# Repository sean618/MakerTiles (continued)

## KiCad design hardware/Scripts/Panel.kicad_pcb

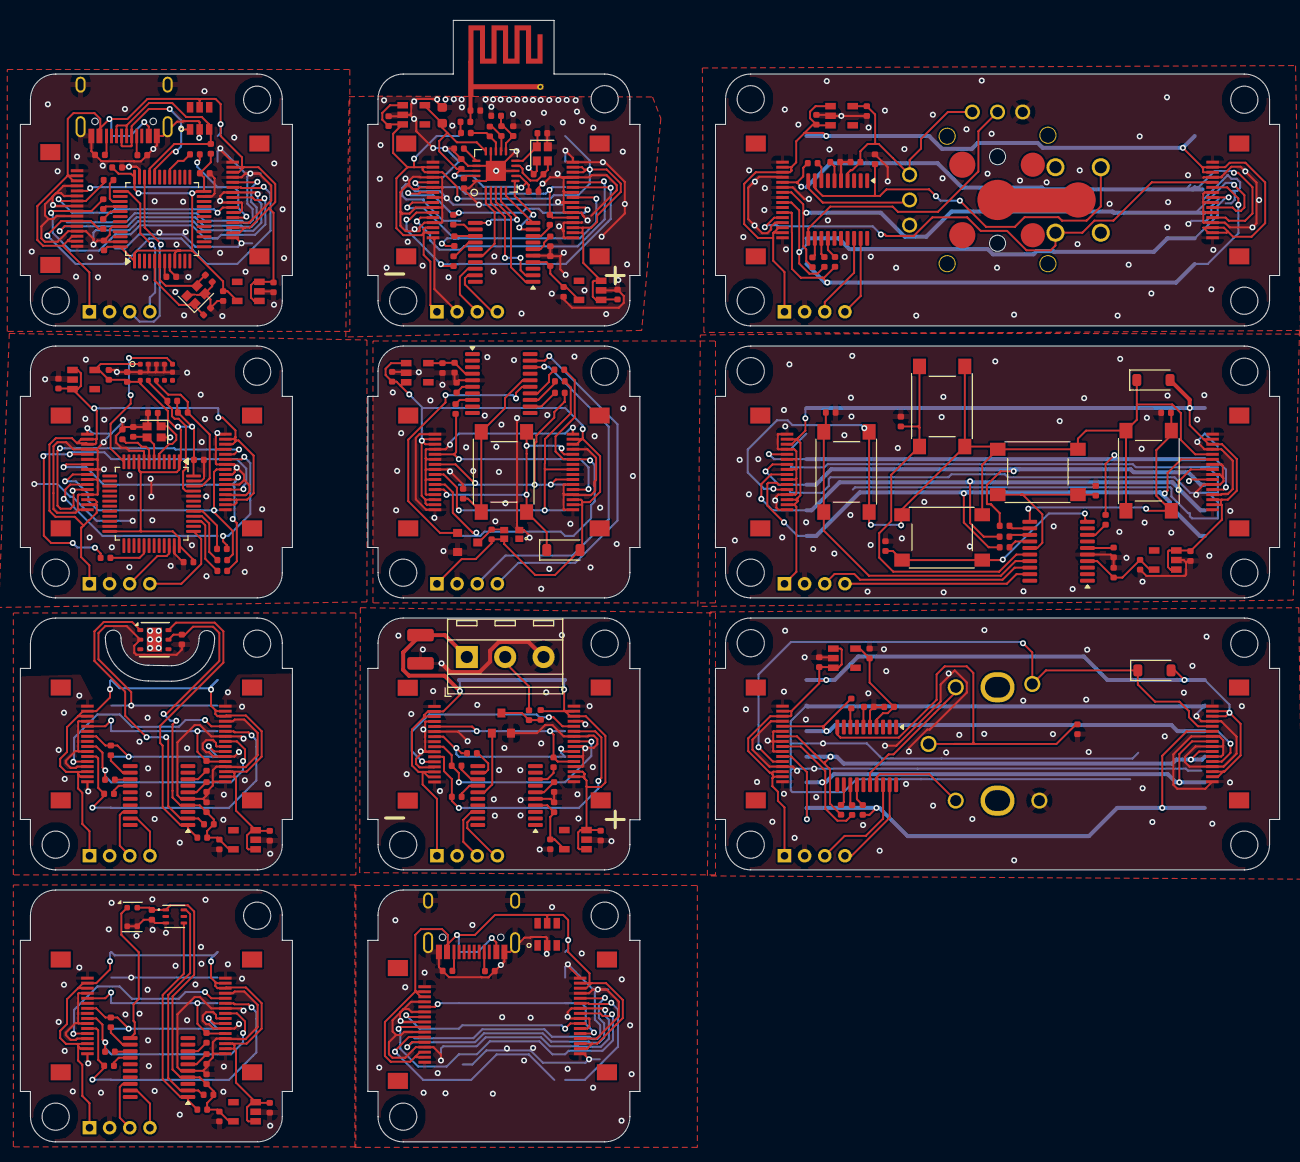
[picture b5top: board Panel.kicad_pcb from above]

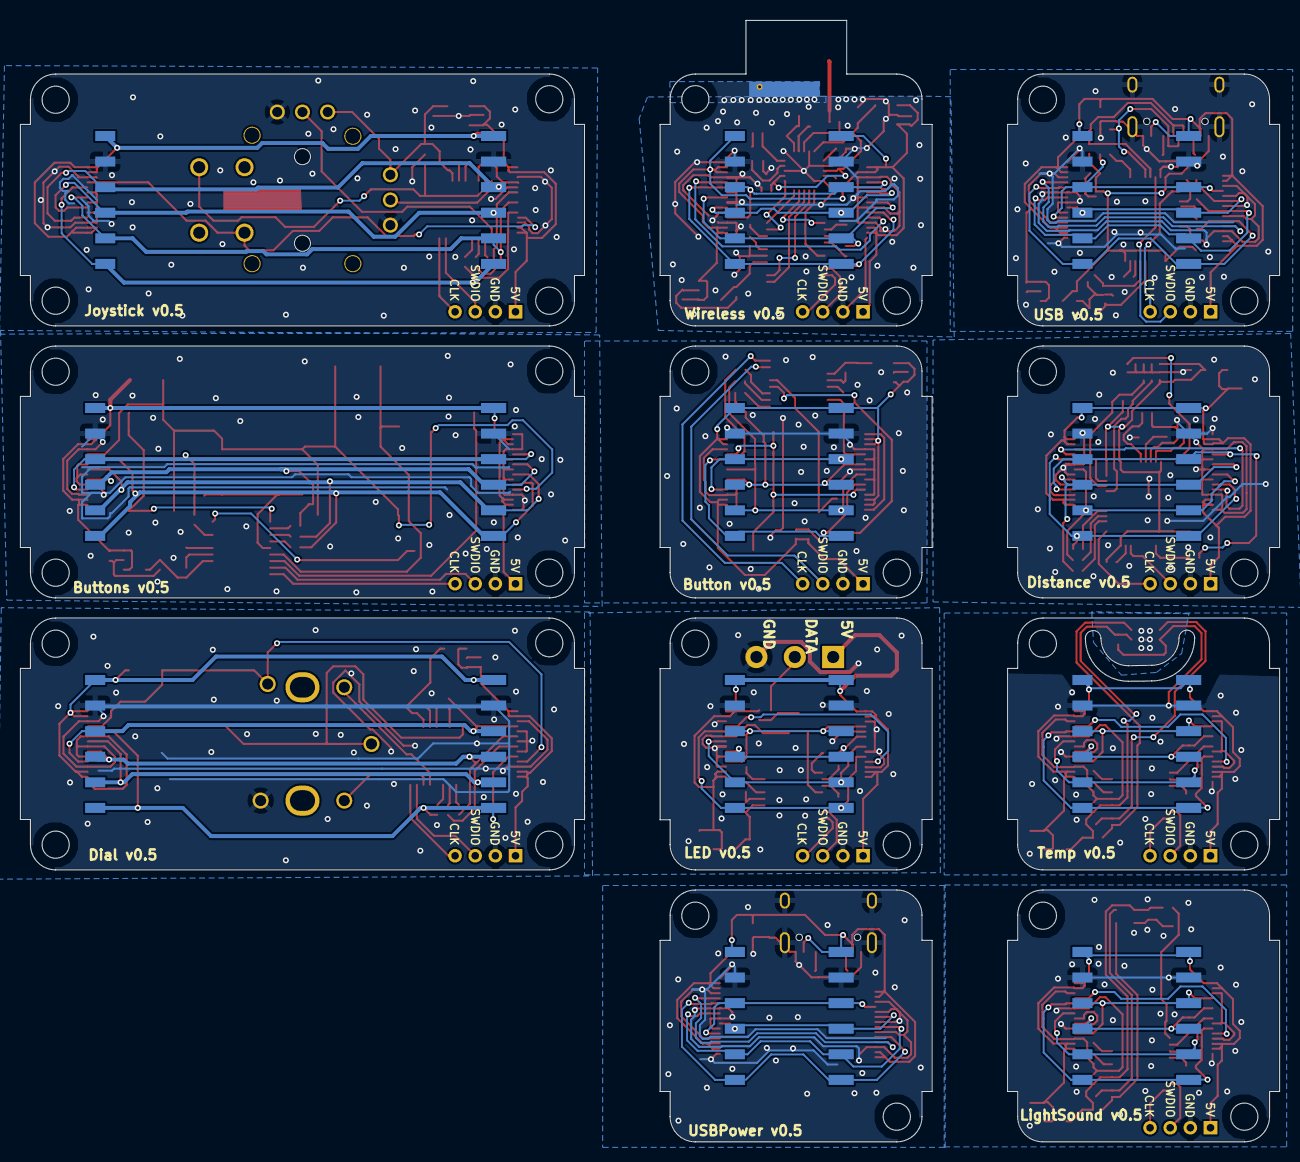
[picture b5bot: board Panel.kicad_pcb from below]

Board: 4 copper layers, 125.0 x 111.3 mm, 273 parts (22 on the bottom side), 208 nets.

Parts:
BTSC1: 0.1uF; C_0402_1005Metric
BTSC2, BTSC8, BTSC9: 4.7uF; C_0402_1005Metric
BTSD2: 1N4148W; D_SOD-123
BTSH1, BTSH2, BTSH3, BTSH4: M2.5MountingHole; MountingHole_2.7mm_M2.5_ISO7380
BTSIGNORE1: Buttons v0.5; BoardText
BTSJ1: 01x06_2.54mm_Male
BTSJ2: 01x06_2.54mm_Female
BTSJ3, BTSJ5: FFC_connector_16p_hinge_lock
BTSJ4: swd_4pin; swd_header
BTSR1, BTSR2, BTSR3, BTSR4: 75R; R_0402_1005Metric
BTSR5, BTSR6, BTSR7, BTSR8, BTSR9: 10K; R_0402_1005Metric
BTSSW1, BTSSW2, BTSSW3, BTSSW4, BTSSW6: button_6x6x7; SW_SPST_PTS645
BTSU2: ME6211C33M5G-N; SOT-23-5
BTSU3: STM32G030F6P6; TSSOP-20_4.4x6.5mm_P0.65mm
BUTC1: 0.1uF; C_0402_1005Metric
BUTC2, BUTC8, BUTC9: 4.7uF; C_0402_1005Metric
BUTD2: ws2812b_1615; WS2812B_1615
BUTD3: 1N4148W; D_SOD-123
BUTH1, BUTH2: M2.5MountingHole; MountingHole_2.7mm_M2.5_ISO7380
BUTIGNORE1: Button v0.5; BoardText
BUTJ1, BUTJ3: FFC_connector_16p_hinge_lock
BUTJ2: 01x06_2.54mm_Male
BUTJ4: swd_4pin; swd_header
BUTJ5: 01x06_2.54mm_Female
BUTQ1: N_MOSFET; SOT-23
BUTR1, BUTR2, BUTR3, BUTR4: 75R; R_0402_1005Metric
BUTR5: 10K; R_0402_1005Metric
BUTR6: 1K; R_0402_1005Metric
BUTSW2: button_6x6x7; SW_SPST_PTS645
BUTU2: ME6211C33M5G-N; SOT-23-5
BUTU3: STM32G030F6P6; TSSOP-20_4.4x6.5mm_P0.65mm
DIAC1: 0.1uF; C_0402_1005Metric
DIAC2, DIAC8, DIAC9: 4.7uF; C_0402_1005Metric
DIAD2: 1N4148W; D_SOD-123
DIAH1, DIAH2, DIAH3, DIAH4: M2.5MountingHole; MountingHole_2.7mm_M2.5_ISO7380
DIAIGNORE1: Dial v0.5; BoardText
DIAJ1, DIAJ2: FFC_connector_16p_hinge_lock
DIAJ3: 01x06_2.54mm_Male
DIAJ4: swd_4pin; swd_header
DIAJ5: 01x06_2.54mm_Female
DIAR1, DIAR2, DIAR3, DIAR4: 75R; R_0402_1005Metric
DIAR5: 10K; R_0402_1005Metric
DIASW7: RotaryEncoder_Switch; RotaryEncoderEC12D
DIAU2: ME6211C33M5G-N; SOT-23-5
DIAU3: STM32G030F6P6; TSSOP-20_4.4x6.5mm_P0.65mm
DISC3, DISC4, DISC5, DISC8, DISC9: 4.7uF; C_0402_1005Metric
DISC6, DISC7: 12pF; C_0402_1005Metric
DISC11: 0.1uF; C_0402_1005Metric
DISH1, DISH2: M2.5MountingHole; MountingHole_2.7mm_M2.5_ISO7380
DISIGNORE1: Distance v0.5; BoardText
DISJ1: 01x06_2.54mm_Male
DISJ2: 01x06_2.54mm_Female
DISJ3, DISJ5: FFC_connector_16p_hinge_lock
DISJ4: swd_4pin; swd_header
DISR5, DISR6: 10K; R_0402_1005Metric
DISR7, DISR8, DISR9, DISR10: 75R; R_0402_1005Metric
DISU1: VL53L3CXV0DH
DISU2: ME6211C33M5G-N; SOT-23-5
DISU3: STM32F103C8T6; LQFP-48_7x7mm_P0.5mm
DISY1: Crystal_16M_small; Crystal_SMD_2016-4Pin_2.0x1.6mm
JOYC1: 0.1uF; C_0402_1005Metric
JOYC2, JOYC8, JOYC9: 4.7uF; C_0402_1005Metric
JOYH1, JOYH2, JOYH3, JOYH4: M2.5MountingHole; MountingHole_2.7mm_M2.5_ISO7380
JOYIGNORE1: Joystick v0.5; BoardText
JOYJ1: 01x06_2.54mm_Male
JOYJ2, JOYJ5: FFC_connector_16p_hinge_lock
JOYJ3: 01x06_2.54mm_Female
JOYJ4: swd_4pin; swd_header
JOYR1, JOYR2, JOYR3, JOYR4: 75R; R_0402_1005Metric
JOYR6: 10K; R_0402_1005Metric
JOYU1: Joystick
JOYU2: ME6211C33M5G-N; SOT-23-5
JOYU3: STM32G030F6P6; TSSOP-20_4.4x6.5mm_P0.65mm
LEDC1: 0.1uF; C_0402_1005Metric
LEDC2, LEDC8, LEDC9: 4.7uF; C_0402_1005Metric
LEDC4: 47uF_16V; C_1210_3225Metric
LEDH1, LEDH2: M2.5MountingHole; MountingHole_2.7mm_M2.5_ISO7380
LEDIGNORE1: LED v0.5; BoardText
LEDIGNORE2: GND; BoardText
LEDIGNORE3: DATA; BoardText
LEDIGNORE4: 5V; BoardText
LEDJ1: 01x06_2.54mm_Male
LEDJ2: TerminalBlock_3P_3.8_black; TerminalBlock_03_P3.81mm_Horizontal
LEDJ3: 01x06_2.54mm_Female
LEDJ4: swd_4pin; swd_header
LEDJ5, LEDJ7: FFC_connector_16p_hinge_lock
LEDQ3: N_MOSFET; SOT-23
LEDR1, LEDR2, LEDR3, LEDR4: 75R; R_0402_1005Metric
LEDR5, LEDR7: 1K; R_0402_1005Metric
LEDU2: ME6211C33M5G-N; SOT-23-5
LEDU3: STM32G030F6P6; TSSOP-20_4.4x6.5mm_P0.65mm
LIGC1: 0.1uF; C_0402_1005Metric
LIGC2, LIGC3, LIGC8, LIGC9: 4.7uF; C_0402_1005Metric
LIGH1, LIGH2: M2.5MountingHole; MountingHole_2.7mm_M2.5_ISO7380
LIGIGNORE1: LightSound v0.5; BoardText
LIGJ1: 01x06_2.54mm_Male
LIGJ2: 01x06_2.54mm_Female
LIGJ3, LIGJ5: FFC_connector_16p_hinge_lock
LIGJ4: swd_4pin; swd_header
LIGR1, LIGR2, LIGR3, LIGR4: 75R; R_0402_1005Metric
LIGR5, LIGR6: 10K; R_0402_1005Metric
LIGU1: LTR-381RGB
LIGU2: ME6211C33M5G-N; SOT-23-5
LIGU3: STM32G030F6P6; TSSOP-20_4.4x6.5mm_P0.65mm
LIGU4: WMM7027ATSN1-4/TR; LGA-4
POWH1, POWH2: M2.5MountingHole; MountingHole_2.7mm_M2.5_ISO7380
POWIC1: USBLC6-4SC6; SOT-23-6
POWIGNORE1: USBPower v0.5; BoardText
POWJ1: 01x06_2.54mm_Male
POWJ2: USB_C_connector_16P; USB_C_Receptacle_16P
POWJ3: 01x06_2.54mm_Female
POWJ5, POWJ6: FFC_connector_16p_hinge_lock
POWR1, POWR2: 5.1K; R_0402_1005Metric
TMPC1: 0.1uF; C_0402_1005Metric
TMPC2, TMPC3, TMPC8, TMPC9: 4.7uF; C_0402_1005Metric
TMPH1, TMPH2: M2.5MountingHole; MountingHole_2.7mm_M2.5_ISO7380
TMPIGNORE1: Temp v0.5; BoardText
TMPJ1: 01x06_2.54mm_Male
TMPJ2: 01x06_2.54mm_Female
TMPJ3, TMPJ5: FFC_connector_16p_hinge_lock
TMPJ4: swd_4pin; swd_header
TMPR1, TMPR2, TMPR3, TMPR4: 75R; R_0402_1005Metric
TMPR5, TMPR6: 10K; R_0402_1005Metric
TMPU1: HDC1080; Texas_PWSON-N6
TMPU2: ME6211C33M5G-N; SOT-23-5
TMPU3: STM32G030F6P6; TSSOP-20_4.4x6.5mm_P0.65mm
USBC1, USBC2, USBC5, USBC8, USBC9: 4.7uF; C_0402_1005Metric
USBC4: 0.1uF; C_0402_1005Metric
USBC6, USBC7: 12pF; C_0402_1005Metric
USBH1, USBH2: M2.5MountingHole; MountingHole_2.7mm_M2.5_ISO7380
USBIC1: USBLC6-4SC6; SOT-23-6
USBIGNORE1: USB v0.5; BoardText
USBJ1: 01x06_2.54mm_Male
USBJ2: USB_C_connector_16P; USB_C_Receptacle_16P
USBJ3: 01x06_2.54mm_Female
USBJ4: swd_4pin; swd_header
USBJ5, USBJ6: FFC_connector_16p_hinge_lock
USBR1, USBR2: 5.1K; R_0402_1005Metric
USBR4, USBR5, USBR6, USBR7: 75R; R_0402_1005Metric
USBR12: 1.5K; R_0402_1005Metric
USBU1: STM32F103C8T6; LQFP-48_7x7mm_P0.5mm
USBU2: ME6211C33M5G-N; SOT-23-5
USBY2: Crystal_16M_small; Crystal_SMD_2016-4Pin_2.0x1.6mm
WIRAE1: Antenna_MIFA_Cypress; Antenna_cypress_MIFA
WIRC1: 0.1uF; C_0402_1005Metric
WIRC2, WIRC8, WIRC9, WIRC11, WIRC12, WIRC15: 4.7uF; C_0402_1005Metric
WIRC3: 33nF; C_0402_1005Metric
WIRC4: 2.2nF; C_0402_1005Metric
WIRC5, WIRC6: 12pF; C_0402_1005Metric
WIRC7: 1pF; C_0402_1005Metric
WIRC10: 1.5pF; C_0402_1005Metric
WIRC13: 22uF_10V; C_0603_1608Metric
WIRC14: 4.7pF; C_0402_1005Metric
WIRH1, WIRH2: M2.5MountingHole; MountingHole_2.7mm_M2.5_ISO7380
WIRIGNORE1: Wireless v0.5; BoardText
WIRJ1: 01x06_2.54mm_Male
WIRJ2: 01x06_2.54mm_Female
WIRJ3, WIRJ5: FFC_connector_16p_hinge_lock
WIRJ4: swd_4pin; swd_header
WIRL1: 8.2nH; C_0402_1005Metric
WIRL3: 3.9nH; C_0402_1005Metric
WIRL4: 2.7nH; C_0402_1005Metric
WIRR1, WIRR2, WIRR3, WIRR4: 120R; R_0402_1005Metric
WIRR6: 22K; R_0402_1005Metric
WIRU1, WIRU2: ME6211C33M5G-N; SOT-23-5
WIRU3: STM32G030F6P6; TSSOP-20_4.4x6.5mm_P0.65mm
WIRU4: NRF24L01; QFN-20-1EP_4x4mm_P0.5mm_EP2.5x2.5mm
WIRY2: Crystal_16M_small; Crystal_SMD_2016-4Pin_2.0x1.6mm

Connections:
BTS_5V: BTSC8.1, BTSD2.2 (A), BTSJ1.1, BTSJ2.6, BTSJ3.2, BTSJ3.3, BTSJ3.14, BTSJ3.15, BTSJ4.1, BTSJ5.2, BTSJ5.3, BTSJ5.14, BTSJ5.15, BTSU2.1 (IN), BTSU2.3 (EN)
BTS_GND: BTSC1.2, BTSC2.2, BTSC8.2, BTSC9.2, BTSJ1.2, BTSJ2.5, BTSJ3.1, BTSJ3.4, BTSJ3.6, BTSJ3.8, BTSJ3.10, BTSJ3.13, BTSJ3.16, BTSJ4.2, BTSJ5.1, BTSJ5.4, BTSJ5.6, BTSJ5.8, BTSJ5.10, BTSJ5.13, BTSJ5.16, BTSR5.1, BTSR6.1, BTSR7.1, BTSR8.1, BTSR9.1, BTSU2.2 (GND), BTSU3.5 (VSS)
BTS_Interrupt5V: BTSD2.1 (K), BTSJ3.12, BTSJ5.12, BTSSW1.2, BTSSW2.2, BTSSW3.2, BTSSW4.2, BTSSW6.2
BTS_MISO: BTSJ1.5, BTSJ2.2, BTSJ3.9, BTSJ5.9, BTSR4.2
BTS_MOSI: BTSJ1.6, BTSJ2.1, BTSJ3.11, BTSJ5.11, BTSR2.2
BTS_Net-(U3-NRST): BTSC1.1, BTSU3.6 (NRST)
BTS_Net-(U3-PA1): BTSR1.1, BTSU3.8 (PA1)
BTS_Net-(U3-PA5): BTSR3.1, BTSU3.12 (PA5)
BTS_Net-(U3-PA6): BTSR4.1, BTSU3.13 (PA6)
BTS_Net-(U3-PA7): BTSR2.1, BTSU3.14 (PA7)
BTS_PS: BTSJ1.3, BTSJ2.4, BTSJ3.5, BTSJ5.5, BTSR1.2
BTS_SCLK: BTSJ1.4, BTSJ2.3, BTSJ3.7, BTSJ5.7, BTSR3.2
BTS_SW1: BTSR5.2, BTSSW2.1, BTSU3.16 (PA11/PA9)
BTS_SW2: BTSR6.2, BTSSW1.1, BTSU3.17 (PA12/PA10)
BTS_SW3: BTSR7.2, BTSSW6.1, BTSU3.11 (PA4)
BTS_SW4: BTSR9.2, BTSSW3.1, BTSU3.15 (PB0/PB1/PB2/PA8)
BTS_SW5: BTSR8.2, BTSSW4.1, BTSU3.10 (PA3)
BTS_SWDCLK: BTSJ4.4, BTSU3.19 (PA14/PA15)
BTS_SWDIO: BTSJ4.3, BTSU3.18 (PA13)
BTS_VDD: BTSC2.1, BTSC9.1, BTSU2.5 (OUT), BTSU3.4 (VDD)
BUT_5V: BUTC8.1, BUTD2.2 (VDD), BUTD3.2 (A), BUTJ1.2, BUTJ1.3, BUTJ1.14, BUTJ1.15, BUTJ2.1, BUTJ3.2, BUTJ3.3, BUTJ3.14, BUTJ3.15, BUTJ4.1, BUTJ5.6, BUTR6.1, BUTU2.1 (IN), BUTU2.3 (EN)
BUT_GND: BUTC1.2, BUTC2.2, BUTC8.2, BUTC9.2, BUTD2.3 (VSS), BUTJ1.1, BUTJ1.4, BUTJ1.6, BUTJ1.8, BUTJ1.10, BUTJ1.13, BUTJ1.16, BUTJ2.2, BUTJ3.1, BUTJ3.4, BUTJ3.6, BUTJ3.8, BUTJ3.10, BUTJ3.13, BUTJ3.16, BUTJ4.2, BUTJ5.5, BUTQ1.2 (S), BUTR5.1, BUTU2.2 (GND), BUTU3.5 (VSS)
BUT_Interrupt5V: BUTD3.1 (K), BUTJ1.12, BUTJ3.12, BUTSW2.2
BUT_LED_DATA: BUTQ1.1 (G), BUTU3.15 (PB0/PB1/PB2/PA8)
BUT_MISO: BUTJ1.9, BUTJ2.5, BUTJ3.9, BUTJ5.2, BUTR4.2
BUT_MOSI: BUTJ1.11, BUTJ2.6, BUTJ3.11, BUTJ5.1, BUTR2.2
BUT_Net-(D2-DIN): BUTD2.4 (DIN), BUTQ1.3 (D), BUTR6.2
BUT_Net-(U3-NRST): BUTC1.1, BUTU3.6 (NRST)
BUT_Net-(U3-PA1): BUTR1.1, BUTU3.8 (PA1)
BUT_Net-(U3-PA5): BUTR3.1, BUTU3.12 (PA5)
BUT_Net-(U3-PA6): BUTR4.1, BUTU3.13 (PA6)
BUT_Net-(U3-PA7): BUTR2.1, BUTU3.14 (PA7)
BUT_PS: BUTJ1.5, BUTJ2.3, BUTJ3.5, BUTJ5.4, BUTR1.2
BUT_SCLK: BUTJ1.7, BUTJ2.4, BUTJ3.7, BUTJ5.3, BUTR3.2
BUT_SW1: BUTR5.2, BUTSW2.1, BUTU3.16 (PA11/PA9)
BUT_SWDCLK: BUTJ4.4, BUTU3.19 (PA14/PA15)
BUT_SWDIO: BUTJ4.3, BUTU3.18 (PA13)
BUT_VDD: BUTC2.1, BUTC9.1, BUTU2.5 (OUT), BUTU3.4 (VDD)
DIA_5V: DIAC8.1, DIAD2.2 (A), DIAJ1.2, DIAJ1.3, DIAJ1.14, DIAJ1.15, DIAJ2.2, DIAJ2.3, DIAJ2.14, DIAJ2.15, DIAJ3.1, DIAJ4.1, DIAJ5.6, DIAU2.1 (IN), DIAU2.3 (EN)
DIA_ENC_A: DIASW7.A, DIAU3.17 (PA12/PA10)
DIA_ENC_B: DIASW7.B, DIAU3.16 (PA11/PA9)
DIA_GND: DIAC1.2, DIAC2.2, DIAC8.2, DIAC9.2, DIAJ1.1, DIAJ1.4, DIAJ1.6, DIAJ1.8, DIAJ1.10, DIAJ1.13, DIAJ1.16, DIAJ2.1, DIAJ2.4, DIAJ2.6, DIAJ2.8, DIAJ2.10, DIAJ2.13, DIAJ2.16, DIAJ3.2, DIAJ4.2, DIAJ5.5, DIAR5.1, DIASW7.C, DIAU2.2 (GND), DIAU3.5 (VSS)
DIA_Interrupt5V: DIAD2.1 (K), DIAJ1.12, DIAJ2.12, DIASW7.S1
DIA_MISO: DIAJ1.9, DIAJ2.9, DIAJ3.5, DIAJ5.2, DIAR4.2
DIA_MOSI: DIAJ1.11, DIAJ2.11, DIAJ3.6, DIAJ5.1, DIAR2.2
DIA_Net-(U3-NRST): DIAC1.1, DIAU3.6 (NRST)
DIA_Net-(U3-PA1): DIAR1.1, DIAU3.8 (PA1)
DIA_Net-(U3-PA5): DIAR3.1, DIAU3.12 (PA5)
DIA_Net-(U3-PA6): DIAR4.1, DIAU3.13 (PA6)
DIA_Net-(U3-PA7): DIAR2.1, DIAU3.14 (PA7)
DIA_PS: DIAJ1.5, DIAJ2.5, DIAJ3.3, DIAJ5.4, DIAR1.2
DIA_SCLK: DIAJ1.7, DIAJ2.7, DIAJ3.4, DIAJ5.3, DIAR3.2
DIA_SW1: DIAR5.2, DIASW7.S2, DIAU3.10 (PA3)
DIA_SWDCLK: DIAJ4.4, DIAU3.19 (PA14/PA15)
DIA_SWDIO: DIAJ4.3, DIAU3.18 (PA13)
DIA_VDD: DIAC2.1, DIAC9.1, DIAU2.5 (OUT), DIAU3.4 (VDD)
DIS_5V: DISC8.1, DISJ1.1, DISJ2.6, DISJ3.2, DISJ3.3, DISJ3.14, DISJ3.15, DISJ4.1, DISJ5.2, DISJ5.3, DISJ5.14, DISJ5.15, DISU2.1 (IN), DISU2.3 (EN)
DIS_GND: DISC3.2, DISC4.2, DISC5.2, DISC6.1, DISC7.1, DISC8.2, DISC9.2, DISC11.1, DISJ1.2, DISJ2.5, DISJ3.1, DISJ3.4, DISJ3.6, DISJ3.8, DISJ3.10, DISJ3.13, DISJ3.16, DISJ4.2, DISJ5.1, DISJ5.4, DISJ5.6, DISJ5.8, DISJ5.10, DISJ5.13, DISJ5.16, DISU1.2 (AVSSVCSEL), DISU1.3 (GND), DISU1.4 (GND), DISU1.6 (GND), DISU1.12 (GND), DISU2.2 (GND), DISU3.8 (VSSA), DISU3.23 (VSS), DISU3.35 (VSS), DISU3.44 (BOOT0), DISU3.47 (VSS), DISY1.2 (GND), DISY1.4 (GND)
DIS_Interrupt5V: DISJ3.12, DISJ5.12
DIS_MISO: DISJ1.5, DISJ2.2, DISJ3.9, DISJ5.9, DISR8.2
DIS_MISO_UC: DISR8.1, DISU3.40 (PB4)
DIS_MOSI: DISJ1.6, DISJ2.1, DISJ3.11, DISJ5.11, DISR9.2
DIS_MOSI_UC: DISR9.1, DISU3.41 (PB5)
DIS_Net-(U3-NRST): DISC11.2, DISU3.7 (NRST)
DIS_OSC_IN: DISC6.2, DISU3.5 (PD0), DISY1.1
DIS_OSC_OUT: DISC7.2, DISU3.6 (PD1), DISY1.3
DIS_PS: DISJ1.3, DISJ2.4, DISJ3.5, DISJ5.5, DISR10.2
DIS_PS_UC: DISR10.1, DISU3.29 (PA8)
DIS_SCL: DISR6.1, DISU1.10 (SCL), DISU3.45 (PB8)
DIS_SCLK: DISJ1.4, DISJ2.3, DISJ3.7, DISJ5.7, DISR7.2
DIS_SCLK_UC: DISR7.1, DISU3.39 (PB3)
DIS_SDA: DISR5.1, DISU1.9 (SDA), DISU3.46 (PB9)
DIS_SWDCLK: DISJ4.4, DISU3.37 (PA14)
DIS_SWDIO: DISJ4.3, DISU3.34 (PA13)
DIS_VDD: DISC3.1, DISC4.1, DISC5.1, DISC9.1, DISR5.2, DISR6.2, DISU1.1 (AVDDVCSEL), DISU1.11 (AVDD), DISU2.5 (OUT), DISU3.1 (VBAT), DISU3.9 (VDDA), DISU3.24 (VDD), DISU3.36 (VDD), DISU3.48 (VDD)
DIS_XSHUT: DISU1.5 (XSHUT), DISU3.12 (PA2)
JOY_5V: JOYC8.1, JOYJ1.1, JOYJ2.2, JOYJ2.3, JOYJ2.14, JOYJ2.15, JOYJ3.6, JOYJ4.1, JOYJ5.2, JOYJ5.3, JOYJ5.14, JOYJ5.15, JOYU2.1 (IN), JOYU2.3 (EN)
JOY_BUTTON: JOYR6.2, JOYU1.D (BUTTON4), JOYU3.9 (PA2)
JOY_GND: JOYC1.2, JOYC2.2, JOYC8.2, JOYC9.2, JOYJ1.2, JOYJ2.1, JOYJ2.4, JOYJ2.6, JOYJ2.8, JOYJ2.10, JOYJ2.13, JOYJ2.16, JOYJ3.5, JOYJ4.2, JOYJ5.1, JOYJ5.4, JOYJ5.6, JOYJ5.8, JOYJ5.10, JOYJ5.13, JOYJ5.16, JOYR6.1, JOYU1.3 (POT1_VLOW), JOYU1.6 (POT2_VLOW), JOYU2.2 (GND), JOYU3.5 (VSS)
JOY_HORIZONTAL: JOYU1.2 (POT1_OUT), JOYU3.11 (PA4)
JOY_Interrupt5V: JOYJ2.12, JOYJ5.12, JOYU1.A (BUTTON1)
JOY_MISO: JOYJ1.5, JOYJ2.9, JOYJ3.2, JOYJ5.9, JOYR4.2
JOY_MOSI: JOYJ1.6, JOYJ2.11, JOYJ3.1, JOYJ5.11, JOYR2.2
JOY_Net-(U3-NRST): JOYC1.1, JOYU3.6 (NRST)
JOY_Net-(U3-PA1): JOYR1.1, JOYU3.8 (PA1)
JOY_Net-(U3-PA5): JOYR3.1, JOYU3.12 (PA5)
JOY_Net-(U3-PA6): JOYR4.1, JOYU3.13 (PA6)
JOY_Net-(U3-PA7): JOYR2.1, JOYU3.14 (PA7)
JOY_PS: JOYJ1.3, JOYJ2.5, JOYJ3.4, JOYJ5.5, JOYR1.2
JOY_SCLK: JOYJ1.4, JOYJ2.7, JOYJ3.3, JOYJ5.7, JOYR3.2
JOY_SWDCLK: JOYJ4.4, JOYU3.19 (PA14/PA15)
JOY_SWDIO: JOYJ4.3, JOYU3.18 (PA13)
JOY_VDD: JOYC2.1, JOYC9.1, JOYU1.1 (POT1_VHIGH), JOYU1.4 (POT2_VHIGH), JOYU2.5 (OUT), JOYU3.4 (VDD)
JOY_VERTICAL: JOYU1.5 (POT2_OUT), JOYU3.10 (PA3)
LED_5V: LEDC4.1, LEDC8.1, LEDJ1.1, LEDJ2.1, LEDJ3.6, LEDJ4.1, LEDJ5.2, LEDJ5.3, LEDJ5.14, LEDJ5.15, LEDJ7.2, LEDJ7.3, LEDJ7.14, LEDJ7.15, LEDR7.1, LEDU2.1 (IN), LEDU2.3 (EN)
LED_GND: LEDC1.2, LEDC2.2, LEDC4.2, LEDC8.2, LEDC9.2, LEDJ1.2, LEDJ2.3, LEDJ3.5, LEDJ4.2, LEDJ5.1, LEDJ5.4, LEDJ5.6, LEDJ5.8, LEDJ5.10, LEDJ5.13, LEDJ5.16, LEDJ7.1, LEDJ7.4, LEDJ7.6, LEDJ7.8, LEDJ7.10, LEDJ7.13, LEDJ7.16, LEDQ3.2 (S), LEDU2.2 (GND), LEDU3.5 (VSS)
LED_Interrupt5V: LEDJ5.12, LEDJ7.12
LED_LED_DATA: LEDQ3.1 (G), LEDU3.15 (PB0/PB1/PB2/PA8)
LED_MISO: LEDJ1.5, LEDJ3.2, LEDJ5.9, LEDJ7.9, LEDR4.2
LED_MOSI: LEDJ1.6, LEDJ3.1, LEDJ5.11, LEDJ7.11, LEDR2.2
LED_Net-(J2-Pin_2): LEDJ2.2, LEDR5.2
LED_Net-(Q3-D): LEDQ3.3 (D), LEDR5.1, LEDR7.2
LED_Net-(U3-NRST): LEDC1.1, LEDU3.6 (NRST)
LED_Net-(U3-PA1): LEDR1.1, LEDU3.8 (PA1)
LED_Net-(U3-PA5): LEDR3.1, LEDU3.12 (PA5)
LED_Net-(U3-PA6): LEDR4.1, LEDU3.13 (PA6)
LED_Net-(U3-PA7): LEDR2.1, LEDU3.14 (PA7)
LED_PS: LEDJ1.3, LEDJ3.4, LEDJ5.5, LEDJ7.5, LEDR1.2
LED_SCLK: LEDJ1.4, LEDJ3.3, LEDJ5.7, LEDJ7.7, LEDR3.2
LED_SWDCLK: LEDJ4.4, LEDU3.19 (PA14/PA15)
LED_SWDIO: LEDJ4.3, LEDU3.18 (PA13)
LED_VDD: LEDC2.1, LEDC9.1, LEDU2.5 (OUT), LEDU3.4 (VDD)
LIG_5V: LIGC8.1, LIGJ1.1, LIGJ2.6, LIGJ3.2, LIGJ3.3, LIGJ3.14, LIGJ3.15, LIGJ4.1, LIGJ5.2, LIGJ5.3, LIGJ5.14, LIGJ5.15, LIGU2.1 (IN), LIGU2.3 (EN)
LIG_GND: LIGC1.2, LIGC2.2, LIGC3.2, LIGC8.2, LIGC9.2, LIGJ1.2, LIGJ2.5, LIGJ3.1, LIGJ3.4, LIGJ3.6, LIGJ3.8, LIGJ3.10, LIGJ3.13, LIGJ3.16, LIGJ4.2, LIGJ5.1, LIGJ5.4, LIGJ5.6, LIGJ5.8, LIGJ5.10, LIGJ5.13, LIGJ5.16, LIGU1.3 (GND), LIGU2.2 (GND), LIGU3.5 (VSS), LIGU4.2 (GND), LIGU4.3 (GND)
LIG_Interrupt5V: LIGJ3.12, LIGJ5.12
LIG_MICROPHONE_ADC: LIGU3.11 (PA4), LIGU4.1 (OUT)
LIG_MISO: LIGJ1.5, LIGJ2.2, LIGJ3.9, LIGJ5.9, LIGR4.2
LIG_MOSI: LIGJ1.6, LIGJ2.1, LIGJ3.11, LIGJ5.11, LIGR2.2
LIG_Net-(U3-NRST): LIGC1.1, LIGU3.6 (NRST)
LIG_Net-(U3-PA1): LIGR1.1, LIGU3.8 (PA1)
LIG_Net-(U3-PA5): LIGR3.1, LIGU3.12 (PA5)
LIG_Net-(U3-PA6): LIGR4.1, LIGU3.13 (PA6)
LIG_Net-(U3-PA7): LIGR2.1, LIGU3.14 (PA7)
LIG_PS: LIGJ1.3, LIGJ2.4, LIGJ3.5, LIGJ5.5, LIGR1.2
LIG_SCL: LIGR5.1, LIGU1.4 (SCL), LIGU3.1 (PB7/PB8)
LIG_SCLK: LIGJ1.4, LIGJ2.3, LIGJ3.7, LIGJ5.7, LIGR3.2
LIG_SDA: LIGR6.1, LIGU1.6 (SDA), LIGU3.2 (PC14/PB9)
LIG_SWDCLK: LIGJ4.4, LIGU3.19 (PA14/PA15)
LIG_SWDIO: LIGJ4.3, LIGU3.18 (PA13)
LIG_VDD: LIGC2.1, LIGC3.1, LIGC9.1, LIGR5.2, LIGR6.2, LIGU1.1 (VDD), LIGU2.5 (OUT), LIGU3.4 (VDD), LIGU4.4 (VDD)
POW_5V: POWIC1.5 (VBUS), POWJ1.1, POWJ2.A4 (VBUS), POWJ2.A9 (VBUS), POWJ2.B4 (VBUS), POWJ2.B9 (VBUS), POWJ3.6, POWJ5.2, POWJ5.3, POWJ5.14, POWJ5.15, POWJ6.2, POWJ6.3, POWJ6.14, POWJ6.15
POW_GND: POWIC1.2 (GND), POWJ1.2, POWJ2.A1 (GND), POWJ2.A12 (GND), POWJ2.B1 (GND), POWJ2.B12 (GND), POWJ2.S1 (SHIELD), POWJ3.5, POWJ5.1, POWJ5.4, POWJ5.6, POWJ5.8, POWJ5.10, POWJ5.13, POWJ5.16, POWJ6.1, POWJ6.4, POWJ6.6, POWJ6.8, POWJ6.10, POWJ6.13, POWJ6.16, POWR1.2, POWR2.1
POW_Interrupt5V: POWJ5.12, POWJ6.12
POW_MISO: POWJ1.5, POWJ3.2, POWJ5.9, POWJ6.9
POW_MOSI: POWJ1.6, POWJ3.1, POWJ5.11, POWJ6.11
POW_Net-(J2-CC1): POWJ2.A5 (CC1), POWR1.1
POW_Net-(J2-CC2): POWJ2.B5 (CC2), POWR2.2
POW_PS: POWJ1.3, POWJ3.4, POWJ5.5, POWJ6.5
POW_SCLK: POWJ1.4, POWJ3.3, POWJ5.7, POWJ6.7
TMP_5V: TMPC8.1, TMPJ1.1, TMPJ2.6, TMPJ3.2, TMPJ3.3, TMPJ3.14, TMPJ3.15, TMPJ4.1, TMPJ5.2, TMPJ5.3, TMPJ5.14, TMPJ5.15, TMPU2.1 (IN), TMPU2.3 (EN)
TMP_GND: TMPC1.2, TMPC2.2, TMPC3.2, TMPC8.2, TMPC9.2, TMPJ1.2, TMPJ2.5, TMPJ3.1, TMPJ3.4, TMPJ3.6, TMPJ3.8, TMPJ3.10, TMPJ3.13, TMPJ3.16, TMPJ4.2, TMPJ5.1, TMPJ5.4, TMPJ5.6, TMPJ5.8, TMPJ5.10, TMPJ5.13, TMPJ5.16, TMPU1.2 (GND), TMPU2.2 (GND), TMPU3.5 (VSS)
TMP_Interrupt5V: TMPJ3.12, TMPJ5.12
TMP_MISO: TMPJ1.5, TMPJ2.2, TMPJ3.9, TMPJ5.9, TMPR4.2
TMP_MOSI: TMPJ1.6, TMPJ2.1, TMPJ3.11, TMPJ5.11, TMPR2.2
TMP_Net-(U3-NRST): TMPC1.1, TMPU3.6 (NRST)
TMP_Net-(U3-PA1): TMPR1.1, TMPU3.8 (PA1)
TMP_Net-(U3-PA5): TMPR3.1, TMPU3.12 (PA5)
TMP_Net-(U3-PA6): TMPR4.1, TMPU3.13 (PA6)
TMP_Net-(U3-PA7): TMPR2.1, TMPU3.14 (PA7)
TMP_PS: TMPJ1.3, TMPJ2.4, TMPJ3.5, TMPJ5.5, TMPR1.2
TMP_SCL: TMPR6.2, TMPU1.6 (SCL), TMPU3.1 (PB7/PB8)
TMP_SCLK: TMPJ1.4, TMPJ2.3, TMPJ3.7, TMPJ5.7, TMPR3.2
TMP_SDA: TMPR5.2, TMPU1.1 (SDA), TMPU3.2 (PC14/PB9)
TMP_SWDCLK: TMPJ4.4, TMPU3.19 (PA14/PA15)
TMP_SWDIO: TMPJ4.3, TMPU3.18 (PA13)
TMP_VDD: TMPC2.1, TMPC3.1, TMPC9.1, TMPR5.1, TMPR6.1, TMPU1.5 (VCC), TMPU2.5 (OUT), TMPU3.4 (VDD)
USB_5V: USBC8.1, USBIC1.5 (VBUS), USBJ1.1, USBJ2.A4 (VBUS), USBJ2.A9 (VBUS), USBJ2.B4 (VBUS), USBJ2.B9 (VBUS), USBJ3.6, USBJ4.1, USBJ5.2, USBJ5.3, USBJ5.14, USBJ5.15, USBJ6.2, USBJ6.3, USBJ6.14, USBJ6.15, USBU2.1 (IN), USBU2.3 (EN)
USB_GND: USBC1.2, USBC2.2, USBC4.1, USBC5.2, USBC6.1, USBC7.1, USBC8.2, USBC9.2, USBIC1.2 (GND), USBJ1.2, USBJ2.A1 (GND), USBJ2.A12 (GND), USBJ2.B1 (GND), USBJ2.B12 (GND), USBJ2.S1 (SHIELD), USBJ3.5, USBJ4.2, USBJ5.1, USBJ5.4, USBJ5.6, USBJ5.8, USBJ5.10, USBJ5.13, USBJ5.16, USBJ6.1, USBJ6.4, USBJ6.6, USBJ6.8, USBJ6.10, USBJ6.13, USBJ6.16, USBR1.2, USBR2.1, USBU1.8 (VSSA), USBU1.23 (VSS), USBU1.35 (VSS), USBU1.44 (BOOT0), USBU1.47 (VSS), USBU2.2 (GND), USBY2.2 (GND), USBY2.4 (GND)
USB_Interrupt5V: USBJ5.12, USBJ6.12
USB_MISO: USBJ1.5, USBJ3.2, USBJ5.9, USBJ6.9, USBR6.2
USB_MISO_UC: USBR6.1, USBU1.40 (PB4)
USB_MOSI: USBJ1.6, USBJ3.1, USBJ5.11, USBJ6.11, USBR4.2
USB_MOSI_UC: USBR4.1, USBU1.41 (PB5)
USB_Net-(J2-CC1): USBJ2.A5 (CC1), USBR1.1
USB_Net-(J2-CC2): USBJ2.B5 (CC2), USBR2.2
USB_Net-(U1-NRST): USBC4.2, USBU1.7 (NRST)
USB_OSC_IN: USBC6.2, USBU1.5 (PD0), USBY2.1
USB_OSC_OUT: USBC7.2, USBU1.6 (PD1), USBY2.3
USB_PS: USBJ1.3, USBJ3.4, USBJ5.5, USBJ6.5, USBR5.2
USB_PS_UC: USBR5.1, USBU1.29 (PA8)
USB_SCLK: USBJ1.4, USBJ3.3, USBJ5.7, USBJ6.7, USBR7.2
USB_SCLK_UC: USBR7.1, USBU1.39 (PB3)
USB_SWDCLK: USBJ4.4, USBU1.37 (PA14)
USB_SWDIO: USBJ4.3, USBU1.34 (PA13)
USB_USB_D+: USBIC1.3 (I/O2), USBJ2.A6 (D+), USBJ2.B6 (D+), USBR12.1, USBU1.33 (PA12)
USB_USB_D-: USBIC1.1 (I/O1), USBJ2.A7 (D-), USBJ2.B7 (D-), USBU1.32 (PA11)
USB_VDD: USBC1.1, USBC2.1, USBC5.1, USBC9.1, USBR12.2, USBU1.1 (VBAT), USBU1.9 (VDDA), USBU1.24 (VDD), USBU1.36 (VDD), USBU1.48 (VDD), USBU2.5 (OUT)
WIR_5V: WIRC8.1, WIRC11.1, WIRJ1.1, WIRJ2.6, WIRJ3.2, WIRJ3.3, WIRJ3.14, WIRJ3.15, WIRJ4.1, WIRJ5.2, WIRJ5.3, WIRJ5.14, WIRJ5.15, WIRU1.1 (IN), WIRU1.3 (EN), WIRU2.1 (IN), WIRU2.3 (EN)
WIR_GND: WIRAE1.2 (GND), WIRC1.2, WIRC2.2, WIRC3.2, WIRC4.2, WIRC5.2, WIRC6.2, WIRC7.2, WIRC8.2, WIRC9.2, WIRC11.2, WIRC12.2, WIRC13.2, WIRC14.2, WIRC15.2, WIRJ1.2, WIRJ2.5, WIRJ3.1, WIRJ3.4, WIRJ3.6, WIRJ3.8, WIRJ3.10, WIRJ3.13, WIRJ3.16, WIRJ4.2, WIRJ5.1, WIRJ5.4, WIRJ5.6, WIRJ5.8, WIRJ5.10, WIRJ5.13, WIRJ5.16, WIRR6.1, WIRU1.2 (GND), WIRU2.2 (GND), WIRU3.5 (VSS), WIRU4.8 (VSS), WIRU4.14 (VSS), WIRU4.17 (VSS), WIRU4.20 (VSS), WIRU4.21 (VSS), WIRY2.2 (GND), WIRY2.4 (GND)
WIR_Interrupt5V: WIRJ3.12, WIRJ5.12
WIR_MISO: WIRJ1.5, WIRJ2.2, WIRJ3.9, WIRJ5.9, WIRR4.2
WIR_MOSI: WIRJ1.6, WIRJ2.1, WIRJ3.11, WIRJ5.11, WIRR2.2
WIR_Net-(AE1-A): WIRAE1.1 (A), WIRC7.1, WIRC10.2
WIR_Net-(C10-Pad1): WIRC10.1, WIRL3.1
WIR_Net-(U3-NRST): WIRC1.1, WIRU3.6 (NRST)
WIR_Net-(U3-PA1): WIRR1.1, WIRU3.8 (PA1)
WIR_Net-(U3-PA5): WIRR3.1, WIRU3.12 (PA5)
WIR_Net-(U3-PA6): WIRR4.1, WIRU3.13 (PA6)
WIR_Net-(U3-PA7): WIRR2.1, WIRU3.14 (PA7)
WIR_Net-(U4-ANT1): WIRL1.1, WIRL4.2, WIRU4.12 (ANT1)
WIR_Net-(U4-ANT2): WIRL1.2, WIRL3.2, WIRU4.13 (ANT2)
WIR_Net-(U4-DVDD): WIRC3.1, WIRU4.19 (DVDD)
WIR_Net-(U4-IREF): WIRR6.2, WIRU4.16 (IREF)
WIR_Net-(U4-VDD_PA): WIRC4.1, WIRC14.1, WIRL4.1, WIRU4.11 (VDD_PA)
WIR_PS: WIRJ1.3, WIRJ2.4, WIRJ3.5, WIRJ5.5, WIRR1.2
WIR_SCLK: WIRJ1.4, WIRJ2.3, WIRJ3.7, WIRJ5.7, WIRR3.2
WIR_SWDCLK: WIRJ4.4, WIRU3.19 (PA14/PA15)
WIR_SWDIO: WIRJ4.3, WIRU3.18 (PA13)
WIR_VDD: WIRC2.1, WIRC12.1, WIRU2.5 (OUT), WIRU3.4 (VDD)
WIR_VDD_NRF: WIRC9.1, WIRC13.1, WIRC15.1, WIRU1.5 (OUT), WIRU4.7 (VDD), WIRU4.15 (VDD), WIRU4.18 (VDD)
WIR_W_CSN: WIRU3.2 (PC14/PB9), WIRU4.2 (CSN)
WIR_W_Enable: WIRU3.16 (PA11/PA9), WIRU4.1 (CE)
WIR_W_INT: WIRU3.9 (PA2), WIRU4.6 (IRQ)
WIR_W_MISO: WIRU3.10 (PA3), WIRU4.5 (MISO)
WIR_W_MOSI: WIRU3.11 (PA4), WIRU4.4 (MOSI)
WIR_W_SCK: WIRU3.1 (PB7/PB8), WIRU4.3 (SCK)
WIR_XC13: WIRC5.1, WIRU4.10 (XC1), WIRY2.1
WIR_XC23: WIRC6.1, WIRU4.9 (XC2), WIRY2.3
